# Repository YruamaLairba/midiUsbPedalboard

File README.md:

# midiUsbPedalboard

This project is to build a configurable midi USB footcontroller with 4
footswitch and 2 inputs for expression pedals. The project is splitted into
subprojects to address differents aspects.

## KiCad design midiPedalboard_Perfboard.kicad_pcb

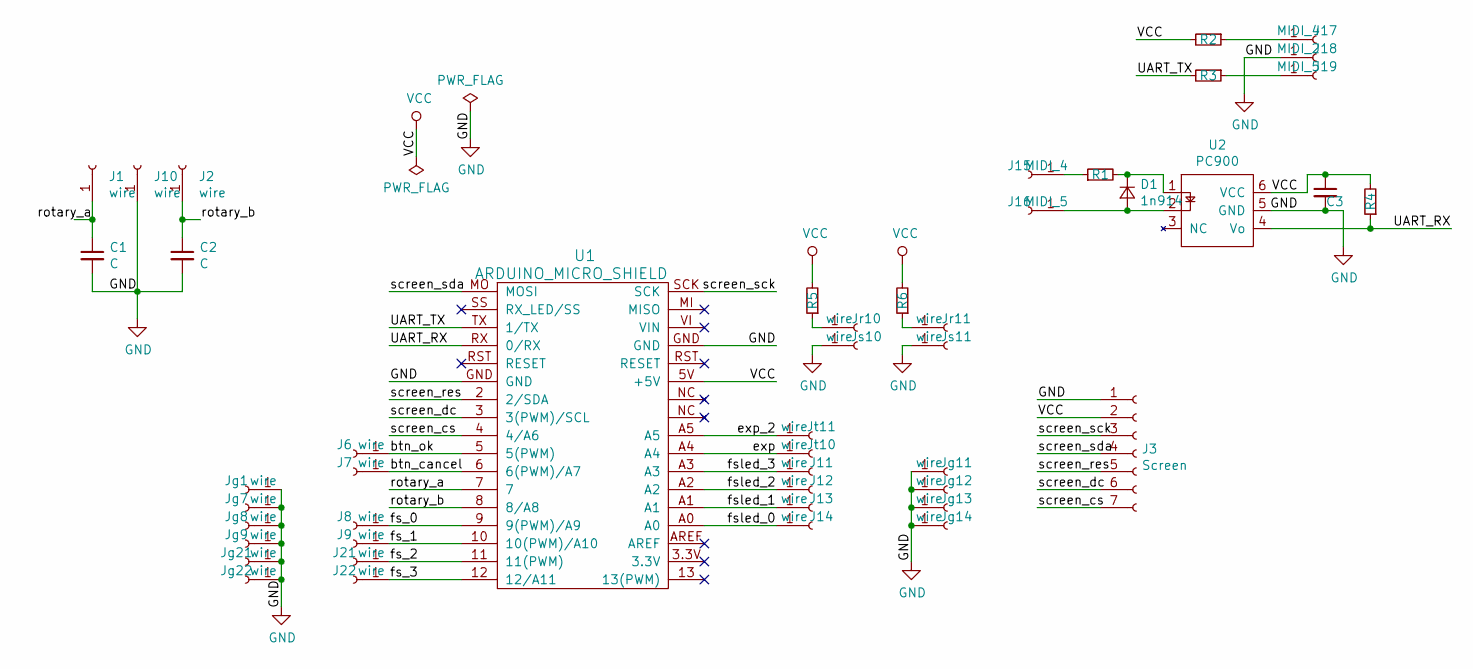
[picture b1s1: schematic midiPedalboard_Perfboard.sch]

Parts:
C1, C2: C; C_Rect_L7.0mm_W2.0mm_P5.00mm
C3: 0.1 uf; C_Rect_L7.0mm_W2.0mm_P5.00mm
D1: 1n914; D_A-405_P2.54mm_Vertical_AnodeUp
J1, J2, J6, J7, J8, J9, J10, J11, J12, J13, J14, J21, J22: wire; SolderWirePad_1x01_Drill0.8mm
J3: Screen; PinSocket_1x07_P2.54mm_Horizontal
J15, J17: MIDI_4; SolderWirePad_1x01_Drill0.8mm
J16, J19: MIDI_5; SolderWirePad_1x01_Drill0.8mm
J18: MIDI_2; SolderWirePad_1x01_Drill0.8mm
Jg1, Jg7, Jg8, Jg9, Jg11, Jg12, Jg13, Jg14, Jg21, Jg22: wire; SolderWirePad_1x01_Drill0.8mm
Jr10, Jr11: wire; SolderWirePad_1x01_Drill0.8mm
Js10, Js11: wire; SolderWirePad_1x01_Drill0.8mm
Jt10, Jt11: wire; SolderWirePad_1x01_Drill0.8mm
R1, R2, R3: 220; R_Axial_DIN0207_L6.3mm_D2.5mm_P2.54mm_Vertical
R4: 280; R_Axial_DIN0207_L6.3mm_D2.5mm_P2.54mm_Vertical
R5, R6: 100; R_Axial_DIN0207_L6.3mm_D2.5mm_P2.54mm_Vertical
U1: ARDUINO_MICRO_SHIELD
U2: PC900; DIP-6_W7.62mm_Socket

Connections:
/UART_RX: R4.1, U1.RX (0/RX), U2.4 (Vo)
/UART_TX: R3.2, U1.TX (1/TX)
/btn_cancel: J7.1, U1.6 (6(PWM)/A7)
/btn_ok: J6.1, U1.5 (5(PWM))
/exp: Jt10.1, U1.A4; also elsewhere on the board
/exp_2: Jt11.1, U1.A5; also elsewhere on the board
/fs_0: J22.1, U1.12 (12/A11)
/fs_1: J21.1, U1.11 (11(PWM))
/fs_2: J9.1, U1.10 (10(PWM)/A10)
/fs_3: J8.1, U1.9 (9(PWM)/A9)
/fsled_0: J14.1, U1.A0
/fsled_1: J13.1, U1.A1
/fsled_2: J12.1, U1.A2
/fsled_3: J11.1, U1.A3
/rotary_a: C1.1, J1.1, U1.7
/rotary_b: C2.1, J2.1, U1.8 (8/A8)
/screen_cs: J3.7, U1.4 (4/A6)
/screen_dc: J3.6, U1.3 (3(PWM)/SCL)
/screen_res: J3.5, U1.2 (2/SDA)
/screen_sck: J3.3, U1.SCK
/screen_sda: J3.4, U1.MO (MOSI)
GND: C1.2, C2.2, C3.2, J3.1, J10.1, J18.1, Jg1.1, Jg7.1, Jg8.1, Jg9.1, Jg11.1, Jg12.1, Jg13.1, Jg14.1, Jg21.1, Jg22.1, Js10.1, Js11.1, U1.GND, U2.5 (GND); also elsewhere on the board
unnamed: D1.1 (K), R1.2, U2.1
unnamed: D1.2 (A), J16.1, U2.2
unnamed: J15.1, R1.1
unnamed: J17.1, R2.1
unnamed: J19.1, R3.1
unnamed: Jr10.1, R5.1
unnamed: Jr11.1, R6.1
VCC: C3.1, J3.2, R2.2, R4.2, R5.2, R6.2, U1.5V (+5V), U2.6 (VCC)

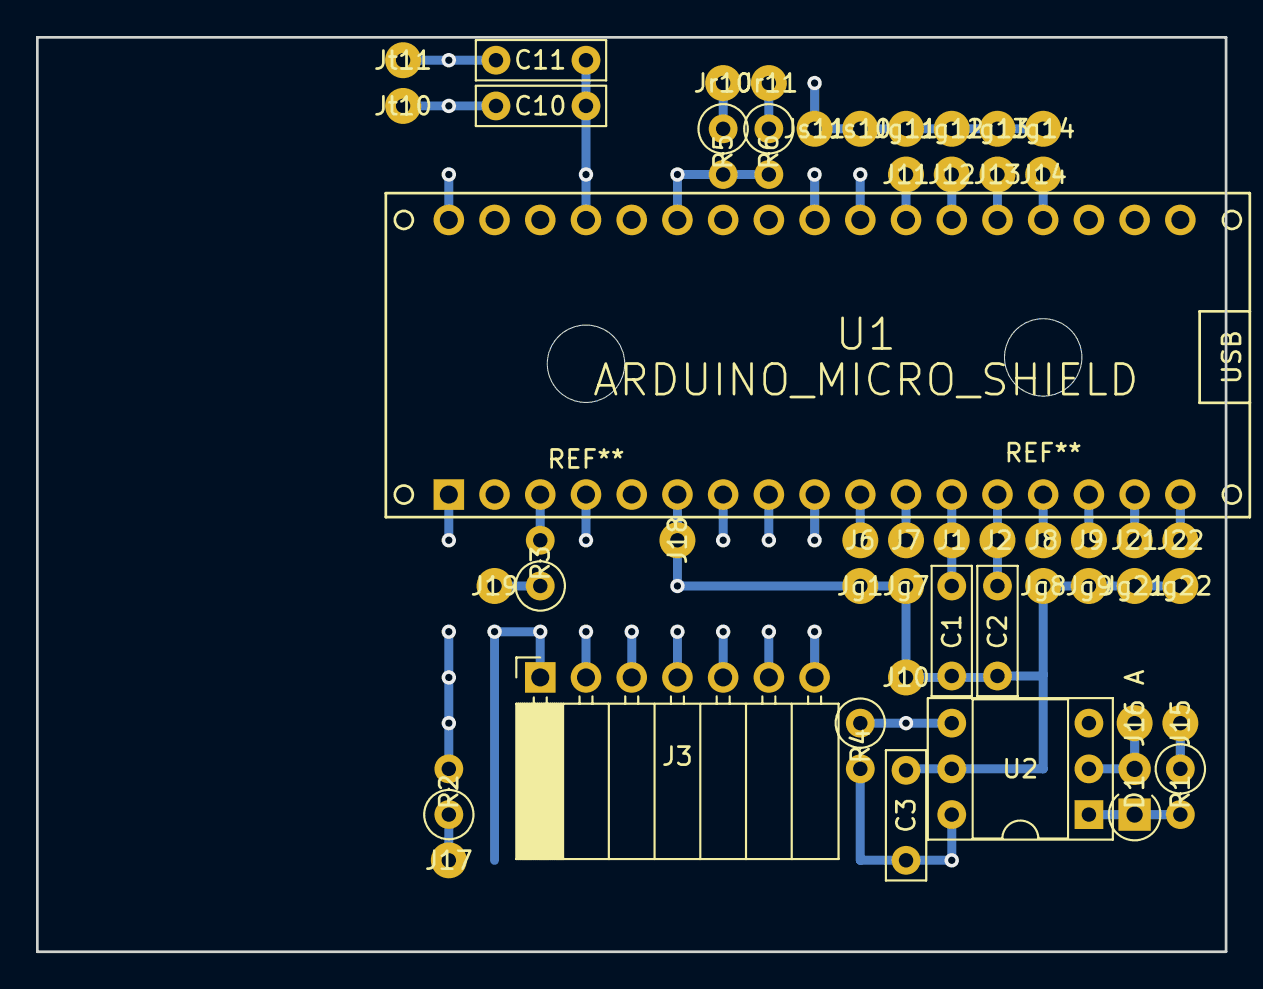
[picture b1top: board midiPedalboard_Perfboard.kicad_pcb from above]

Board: 8 copper layers, 66.0 x 50.8 mm, 49 parts (0 on the bottom side), 30 nets.

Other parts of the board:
C10, C11: 100n; C_Rect_L7.0mm_W2.0mm_P5.00mm

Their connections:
/exp: C10.1; also elsewhere on the board
/exp_2: C11.1; also elsewhere on the board
GND: C10.2, C11.2; also elsewhere on the board

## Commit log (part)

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2017-03-28 initialization with something not bad
2017-04-04 change sign of "selection" to allow more items
    change sign of variable selection to allow more selectable items
2017-04-04 moving class declaration of menus in a header
2017-04-04 added class to value from an enumeration
2017-04-04 change the active menu is now done with a method
2017-04-06 remove public access to all classes members
    all "public" attribute of data member are remplaced by "private" or "protected"
2017-04-13 some change in menus, particularly swSelect
2017-04-20 adding 2 submenu to configure fs and exp
    adding 2 submenu to configure footswitch and expression pedal
2017-05-11 removing some trailing space
2017-05-14 Creating a class prototype for the "mainConf" menu
2017-05-14 Modify "MenuPreseLoad" ctor, add to "MenuMainConf"
2017-05-16 create MenuPresetSave and adding it to mainConf
2017-05-17 modify MenuSwSelect, add it to MenuMainConf
2017-05-17 remove custom warning about MenuMainConf
2017-05-17 Modify MenuFsConfig, add it to MenuSwSelect
2017-05-17 modify MenuExpConfig and fix MenuSwSelect
2017-05-18 create MenuFsMode, add it to MenuFsConfig
2017-05-18 create MenuExpCommand and Mode, add it to MenuExpConfig
2017-05-18 remove or adjust some #warning
2017-05-22 Implement many fonction of Preset for sw conf
2017-05-25 Modify MenuSwSelect to use data of preset class
2017-05-25 Connect all "Fs" and "Exp" menus to preset
2017-05-25 Put ptr to a MenuSwSelect to all it child menus
2017-05-25 Show Exp or Fs number in Menu*Config
2017-06-01 Add debug info in preset class
2017-06-01 finish some method of MenuFsCommand
2017-06-01 add debug info for exp
2017-06-01 finishing some method of MenuExpMode
2017-06-08 create skeleton for preset save and load
2017-06-08 connect MenuPresetLoad and Save to the preset
2017-06-08 add method to get total number of preset
2017-06-22 Reoder attribute, change litteral val to symbolic
2017-07-20 first try with FS, it works but need debouncing. Makefile broken
2017-08-03 fix makefile, use of arduino 1.8.3
2017-08-09 fs now send message, led feedback...
    but led feedback is sensless with "single mode"
2017-08-09 gather all digitalRead()
2017-08-10 deboucing protoype on Ok et CANCEl button
2017-08-16 Debounce coder and footswitch.
    Values choice for deboucing are arbitrary
2017-08-17 add duration measure for handling a FS
    to show the long duration of sending a midi USB message when USb connect but
    no apllication get the midi data on computer side.
2017-08-17 enable display,just display the default image
2017-08-19 Adapt menuMainConf to display it on the display
2017-08-20 Add OPTIMIZATION_LEVEL flag. Use 's'(default)
2017-08-20 display menus load and save to OLED display
2017-08-20 display menu swSelect on OLED display
2017-08-20 display menus fs anf exp config on OLED display
    i didn't use a display offset as this menus aren't supposed to grow
2017-08-20 fix, i forgot to reset displayOffset
2017-08-23 display menu for exp and fs mode on display
    bug, when usb is connected, trying to confire exp land in wrong menu, i
    suspect a memory overflow.
2017-08-31 Change value for rotary coder debouncing
2017-09-06 fix a typo in a header guard
2017-09-06 move constant definition to .h
2017-09-06 use cst value from setup in midiPedalboard.ino
2017-09-06 use "setup" cst in display
2017-09-07 implement preset load/save in EEPROM
    maybe footswitch state update is missing
2017-09-07 improve the way leds lit depending on fsConfig
2017-09-14 start project with a draft
2017-09-14 swap x and y coordinate
2017-09-20 Create module for fooswitch
2017-09-27 better looking footswitch
2017-09-27 use module for each part of the box.
    and each art are builded from an extruded 2D shape
2017-09-27 use a variable for thickness
2017-09-27 create finger beetween low_top and low_front
2017-09-27 use variable for step height
2017-09-27 create finger between high_front and sides
2017-09-27 create fingers between rear and sides
2017-09-27 using var for finger between low_front and low top
2017-09-27 create finger between rear and high_top
2017-09-27 create fingers between high_top and sides
2017-09-27 change fs design to avoid bug with difference
2017-09-27 put all footswitch as background element
2017-09-28 design already existing angle bracket
2017-09-28 use var to adjust distance between fs and sides
2017-10-04 create bottom
2017-10-04 bug fix + angle bracket for bottom
2017-10-11 add hole for cable.
2017-10-12 fix error one angle bracket hole
2017-10-12 refactoring, separate module in 2D and 3D shape
2018-02-08 add holes diameter
2018-02-08 fix an error causing glitch in preview
2018-02-08 remake opening/hole for screen
2018-04-26 add M4 holes to low_top
2018-04-26 add M4 holes to low_front
2018-04-26 add M4 holes to rear
2018-04-26 add M4 holes to left
2018-04-26 add M4 holes to right
2018-04-26 rearrange high_top code
2018-05-02 add M4 holes on high top
2018-05-02 replace 4 angle_bracket_simple with 2 angle_bracket_double
2018-05-02 duplicat some bracket
2018-05-03 add or chnage some bracket
2018-05-03 adjust M4 holes on high top
2018-05-03 adjust M4 holes on low front
2018-05-03 adjust M4 holes on high front and change hole for cable
2018-05-06 change some M4 holes to left
2018-05-06 change some M4 holes of right panel
2018-06-13 use enum for fsMode
2018-06-20 remove commented or useless code about rotarycoder
2018-06-21 draft, Footswitch::read jut do momentary switch
2018-06-23 improve read and set_mode (debouncing, more mode)
2018-06-27 implement "single" cases for Fooswtich::Read()
2018-07-05 change footswitch and preset for save and load
2018-07-05 update menus for fs config
2018-07-05 fix an error for preset load
2018-07-08 fix/improve debouncing
2018-07-12 remove useless comment
2018-07-12 cleaning code that shouldn't be used
2018-07-13 add midi channel selection
2018-07-19 Preset now saved from the end of the eeprom +debug
2018-07-19 eeprom_congig.h for memory mapping
2018-07-19 save midi channel to eeprom and load at init
2018-07-25 create class/file for expression pedal
2018-07-25 update preset classe to take care of expPedal
2018-07-26 check validity of setters value, else force valid
2018-07-26 expPedal now ouput value to midi
2018-08-01 deadzone and delay to avoid to many midi message
2018-08-01 rename for coherent file naming style
2018-08-09 fix no fs led lighting when preset load on startup
2018-08-09 change read to process for fs
2018-08-10 create macro to enable warning in specific section
2018-08-11 create macros to disable many warning for specific section
2018-08-11 enclose Arduino lib header to avoid warnings from them
2018-08-11 remove some useless #warning
2018-08-15 remove some useless piece of code
2018-08-15 use a clas to handle ok and cancel button
2018-08-15 starting the new menusytem with one menu
2018-08-16 remove old menus files, create 2 submenus
2018-08-16 create and add menu_load_preset
2018-08-16 measure some timing in DEBUG
2018-08-16 create and add menu_global_setting_
2018-08-19 change "selection_max" to "get_nb_item()"
2018-08-19 fix a bug on debouncing
2018-08-19 add menu for exp setting
2018-08-20 create and add menu_fs_mode
2018-08-20 create and add exp_command and exp_mode menu
2018-08-20 create and add menu midi channel
2018-08-21 create accessor for fs and exp pedal
2018-08-21 have a pointer to controller_system in menu_system
2018-08-21 nesting class Menu declaration in MenuSystem
2018-08-22 fix void instead uint8_t on accessor
2018-08-22 menu_system can now configure fs or exp
2018-08-23 enable midi channel configuration
2018-08-24 gather preset management into controller_system
2018-08-24 fix a warning in push_button
2018-08-24 fix warning about sign conversion
2018-08-24 add README and LICENSE
2018-08-24 fix markdown in README.md
2018-08-25 make the root menu directly displayed at boot
2018-08-26 use Serial1 to transmit midi message
2018-08-29 Start Serial1 interface only when sending midi
2018-08-29 split files for modules, preview, and export
2018-08-29 remove 3D view from modules file
2018-08-30 rename files
2018-08-30 put connector placeholder in 3D view
2018-08-30 put footswitch in 3D preview
2018-08-30 put angle bracket in 3D preview
2018-08-30 remove some useless commented code
2019-02-25 keep only a skeleton and some usefull modules
2019-02-25 add fingers to the top
2019-02-25 improve fingers
2019-02-27 start front panel, fix invert option of finger mod
2019-02-27 add fingers between front and left (solve collision)
2019-02-27 add rear panel without connector clearance
2019-02-27 add right panel
2019-02-27 add connector hole and clearance
2019-02-27 parametrize finger size
2019-02-27 add Footswitch and connector to preview
2019-02-28 create a crappy parametrizable angle bracket
2019-02-28 use ma_bracket in the preview
2019-03-06 put corner bracket, work around to have transparency view
2019-03-06 create a proxy modul for screw
2019-03-06 add screw in preview
2019-03-06 create corner bracket module
2019-03-06 put new corner bracket in the preview instead
2019-03-06 completly remove the old angle bracket
2019-03-13 add hole for exp pedal connector
2019-03-14 parametrise connector pos
2019-03-14 parametrize jack hole position for exp pedal
2019-03-20 move connector position (avoid collision)
2019-03-20 fix usb connector and color external element
2019-03-20 file juste for export corner_bracket
2019-03-27 use recommended tape drill dimension for M4
2019-04-17 add MenuFsSetting item and rename class & obj
2019-04-18 enum class, getter and setter for fsCmdTyp
2019-04-18 change fsConfig to take care of cmd_typ
2019-04-20 split subprocess per message type, midi_send_cvm
2019-04-21 adapt MenuFsCmdVal depending CC or pgm
2019-04-21 simplify fsCmdTyp_t delcaration
2019-04-21 mmc : enum , getter setter
2019-04-21 add missings cases in switch
2019-04-21 add accessor to get fooswitch
2019-04-21 dirty change in menu to qucly test mmc
2019-04-24 implement MMC toggled message
2019-05-01 swap screen connectors to one connectors
2019-05-01 move hole, connect everything
2019-05-02 some placment and connection
2019-05-02 rotate the design
2019-05-02 move pc900 part
2019-05-02 move sticker
2019-05-08 move sticker 2
2019-05-16 adjust jack hole,jack proxy , move conncetors
2019-05-20 create and place reinforcing bracket
2019-05-20 reinforcment more parametrizable & M4 holes
2019-05-20 adjust reinforcement to avoid issue with buttons
2019-05-20 fix a calculation error for reinforcment hole on the rear
2019-05-20 better jack connector proxy
2019-07-04 fix internal rst wire
2019-07-04 condensator for adc filtering
2019-07-31 change pinout
2019-07-31 start to split menuCmdVal for eache message type
2019-07-31 ooops, fs connection order was reverted
2019-07-31 improve display of menufssetting
2019-07-31 new menu for pgm val (pgm works!)
2019-07-31 reset footswitch when cmd_typ change to avoid inconsistensy
2019-08-01 create menu, accessor to change expcmdtyp
2019-08-01 add expcmdtyp menu to expsettingmenu
2019-08-01 adapt display of exp setting menu to expcmdtyp value
2019-08-07 refactore to extract some midi function from footswitch
2019-08-07 use midi_send_cvm to send exp_pedal cc
2019-08-07 implement pitch bend on exp_pedal
2019-08-08 add some DEBUG in the ino, remove some useless things
2019-08-08 menu to select exp to calibrate
2019-08-11 menu for toes calibration, print the raw exp value
    need to redesign menu system to refresh regularly this menu
2019-08-11 MneuExpCalSel, fix displayed number of exp pedal
2019-08-11 create accessors for exp pedal calibrations
2019-08-11 exp toes value can now be set using menu
2019-08-11 heel pos calibration can now be set from menu
    need to fix a visual glitch
2019-08-11 fix display glitch in some menu
2019-08-11 avoid to send same mesage twice,
    and fix a potential overflow when mapping value for pb
2019-08-12 ugly trick to refresh toes an heel calib menu
2019-08-12 differenciate exp pedal for exp_refresh
    doesn't work when using arduino makefile
2019-08-28 oops, now a real README.md with a real description
2019-08-28 remove a unused file
2019-08-28 Warning about the broken firmware
2019-09-04 replace the lib but screen now flickering
2019-09-04 directly fully overwrite screen to avoid flicker
2019-09-05 remove warning about broken firmware, reformat
2019-09-05 Sorry meessage and typo fix
